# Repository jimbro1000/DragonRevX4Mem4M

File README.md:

# Dragon 256 rev X4 Plus Memory Card #

This repository contains the hardware design
for a heavily revised Dragon 32 computer
memory board.

The design is most definitely experimental
and absolutely unproven

## Design ##

The board replaces the onboard memory
configuration used in early rev X4 PCBs

The bus connection supports a hypothetical
16MB but this is not currently practical

Even with 4MB on this card that main board
only contains logic to address 1MB but will
be expanded to control the full 4MB ASAP.

The remaining 12MB is intended for expansion
slots.

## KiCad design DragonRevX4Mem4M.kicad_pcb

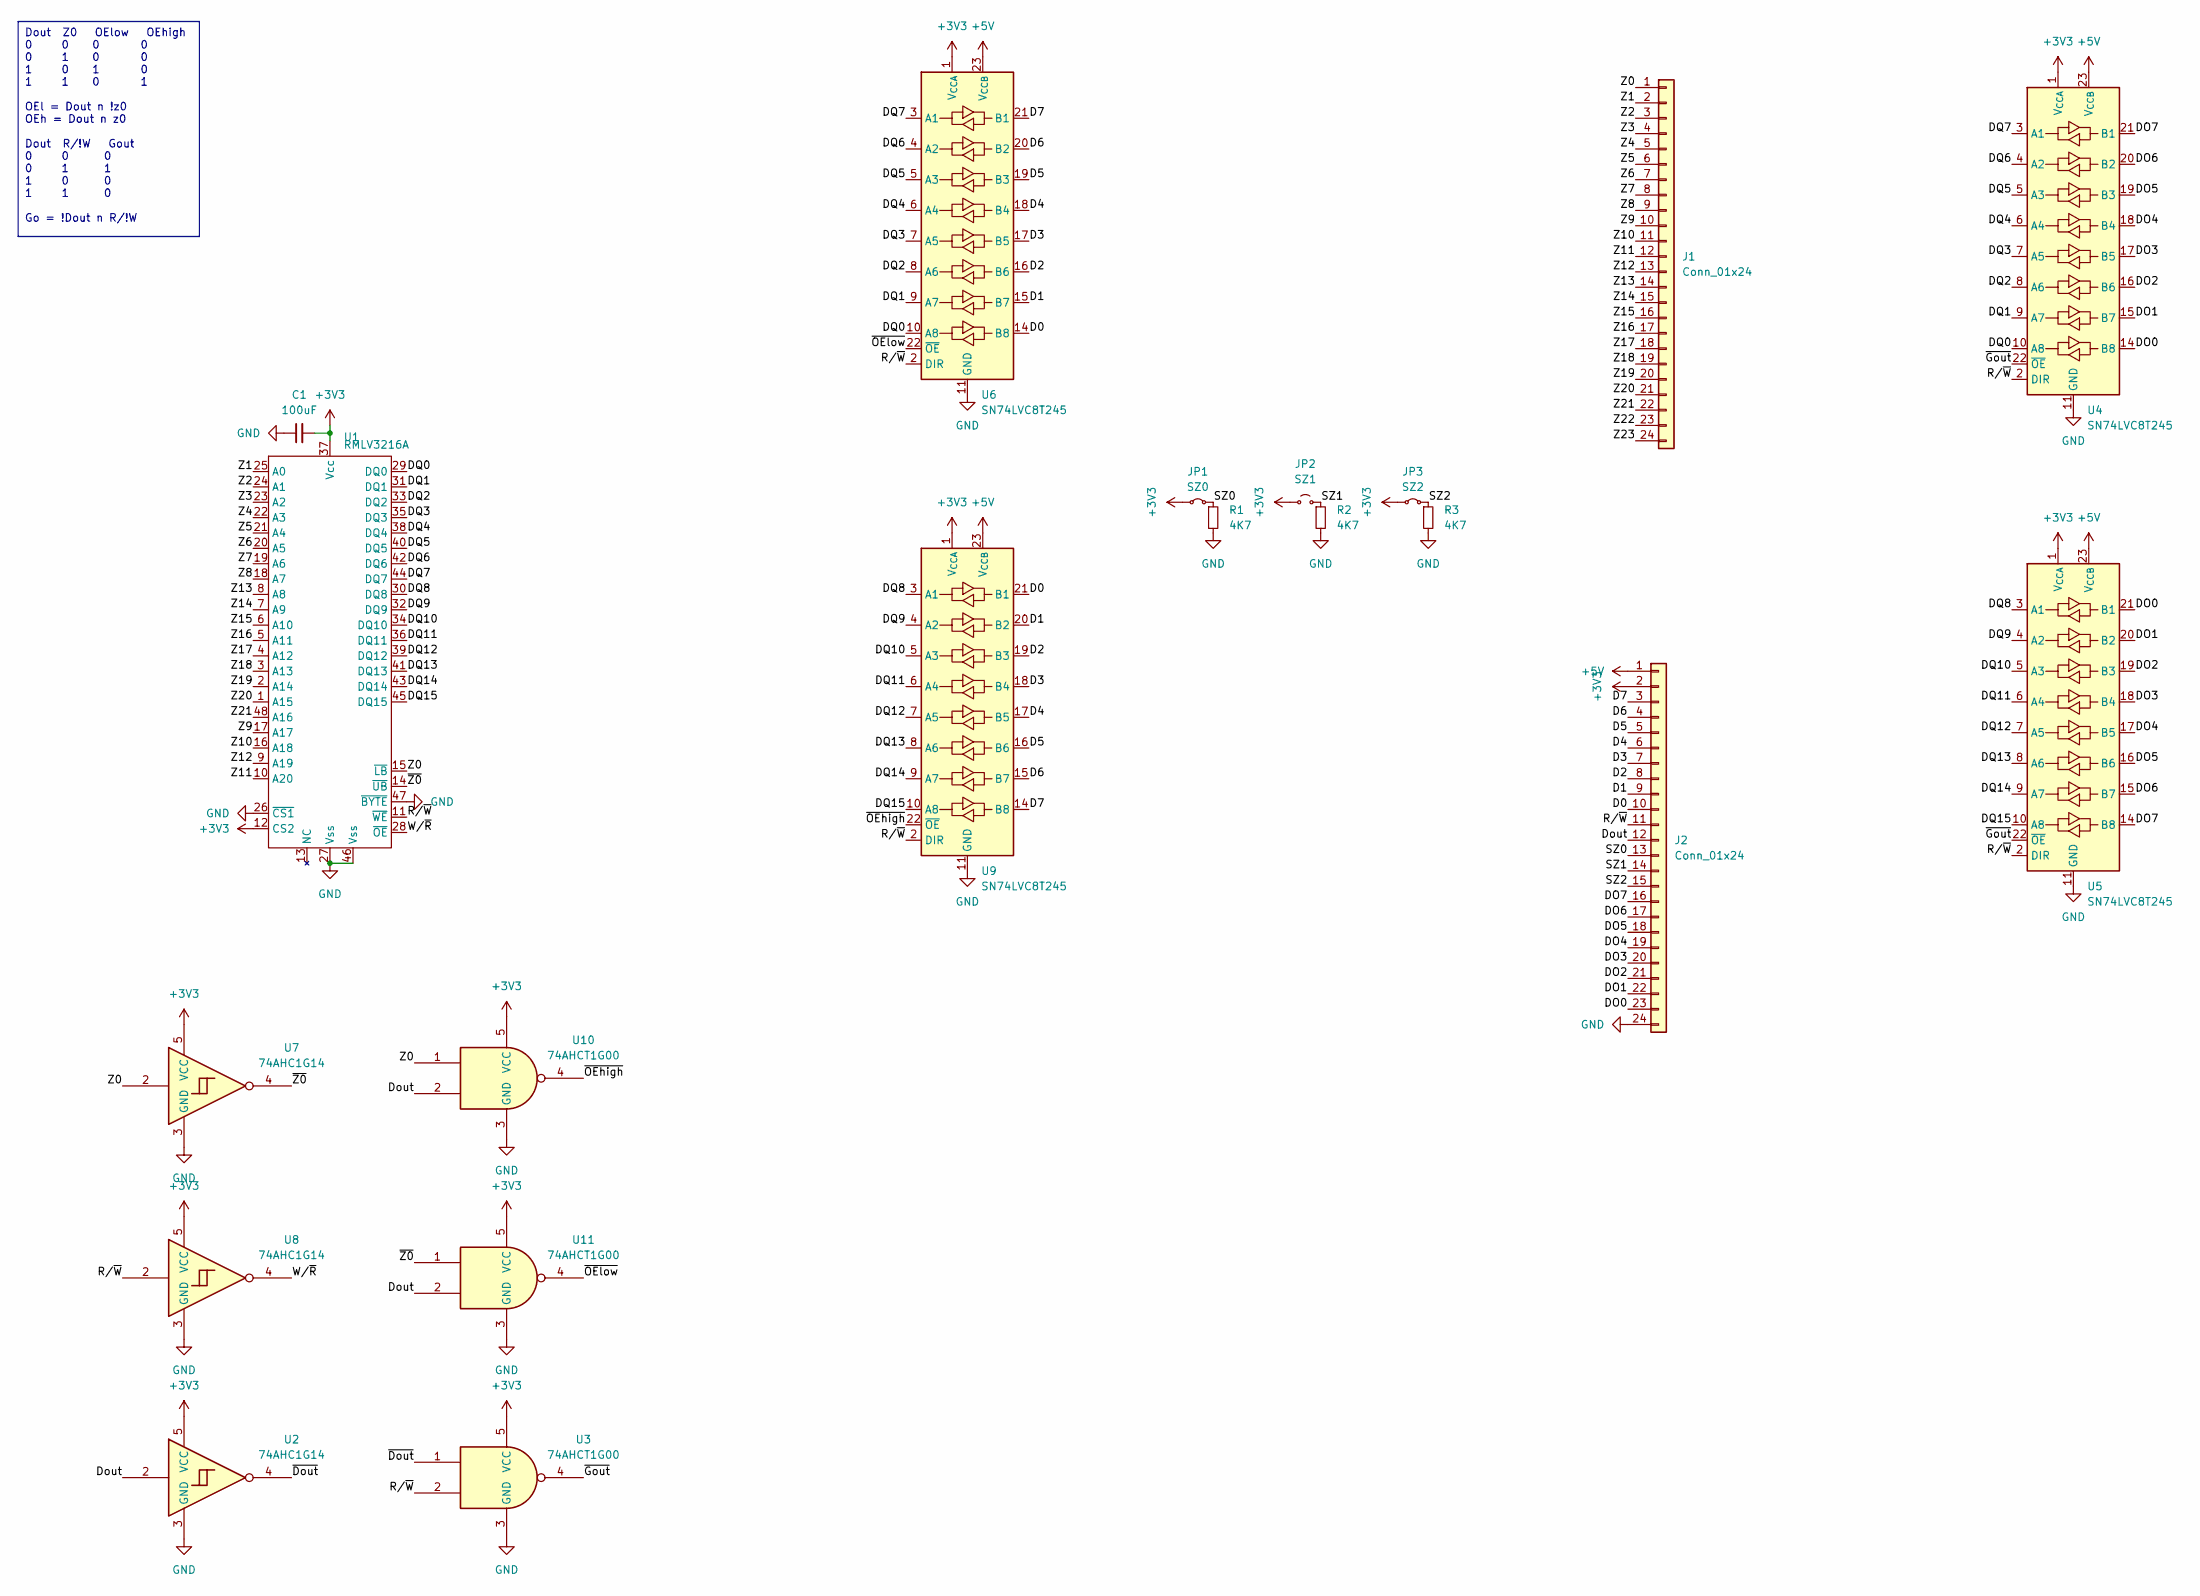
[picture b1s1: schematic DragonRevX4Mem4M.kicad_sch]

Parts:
C1: 100uF; C_0805_2012Metric
J1, J2: Conn_01x24; PinHeader_1x24_P1.27mm_Vertical
JP1: SZ0; SolderJumper-2_P1.3mm_Bridged_Pad1.0x1.5mm
JP2: SZ1; SolderJumper-2_P1.3mm_Open_Pad1.0x1.5mm
JP3: SZ2; SolderJumper-2_P1.3mm_Bridged_Pad1.0x1.5mm
R1, R2, R3: 4K7; C_0603_1608Metric
U1: RMLV3216A; TSOP-I-48_18.4x12mm_P0.5mm; DigiKey RMLV3216AGSA-5S2#AA0-ND
U2, U7, U8: 74AHC1G14; SOT-23-5_HandSoldering; DigiKey 296-1112-1-ND
U3, U10, U11: 74AHCT1G00; SOT-23-5_HandSoldering; DigiKey 296-1111-1-ND
U4, U5, U6, U9: SN74LVC8T245; TSSOP-24_4.4x5mm_P0.4mm; DigiKey 1727-4417-1-ND

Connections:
+3V3: C1.2, J2.2, JP1.1 (A), JP2.1 (A), JP3.1 (A), U1.12 (CS2), U1.37 (Vcc), U2.5 (VCC), U3.5 (VCC), U4.1 (V_{CCA}), U5.1 (V_{CCA}), U6.1 (V_{CCA}), U7.5 (VCC), U8.5 (VCC), U9.1 (V_{CCA}), U10.5 (VCC), U11.5 (VCC)
+5V: J2.1, U4.23 (V_{CCB}), U4.24 (V_{CCB}), U5.23 (V_{CCB}), U5.24 (V_{CCB}), U6.23 (V_{CCB}), U6.24 (V_{CCB}), U9.23 (V_{CCB}), U9.24 (V_{CCB})
/D0: J2.10, U6.14 (B8), U9.21 (B1)
/D1: J2.9, U6.15 (B7), U9.20 (B2)
/D2: J2.8, U6.16 (B6), U9.19 (B3)
/D3: J2.7, U6.17 (B5), U9.18 (B4)
/D4: J2.6, U6.18 (B4), U9.17 (B5)
/D5: J2.5, U6.19 (B3), U9.16 (B6)
/D6: J2.4, U6.20 (B2), U9.15 (B7)
/D7: J2.3, U6.21 (B1), U9.14 (B8)
/DO0: J2.23, U4.14 (B8), U5.21 (B1)
/DO1: J2.22, U4.15 (B7), U5.20 (B2)
/DO2: J2.21, U4.16 (B6), U5.19 (B3)
/DO3: J2.20, U4.17 (B5), U5.18 (B4)
/DO4: J2.19, U4.18 (B4), U5.17 (B5)
/DO5: J2.18, U4.19 (B3), U5.16 (B6)
/DO6: J2.17, U4.20 (B2), U5.15 (B7)
/DO7: J2.16, U4.21 (B1), U5.14 (B8)
/DQ0: U1.29 (DQ0), U4.10 (A8), U6.10 (A8)
/DQ1: U1.31 (DQ1), U4.9 (A7), U6.9 (A7)
/DQ2: U1.33 (DQ2), U4.8 (A6), U6.8 (A6)
/DQ3: U1.35 (DQ3), U4.7 (A5), U6.7 (A5)
/DQ4: U1.38 (DQ4), U4.6 (A4), U6.6 (A4)
/DQ5: U1.40 (DQ5), U4.5 (A3), U6.5 (A3)
/DQ6: U1.42 (DQ6), U4.4 (A2), U6.4 (A2)
/DQ7: U1.44 (DQ7), U4.3 (A1), U6.3 (A1)
/DQ8: U1.30 (DQ8), U5.3 (A1), U9.3 (A1)
/DQ9: U1.32 (DQ9), U5.4 (A2), U9.4 (A2)
/DQ10: U1.34 (DQ10), U5.5 (A3), U9.5 (A3)
/DQ11: U1.36 (DQ11), U5.6 (A4), U9.6 (A4)
/DQ12: U1.39 (DQ12), U5.7 (A5), U9.7 (A5)
/DQ13: U1.41 (DQ13), U5.8 (A6), U9.8 (A6)
/DQ14: U1.43 (DQ14), U5.9 (A7), U9.9 (A7)
/DQ15: U1.45 (DQ15), U5.10 (A8), U9.10 (A8)
/Dout: J2.12, U2.2, U10.2, U11.2
/R/~W: J2.11, U1.11 (~WE), U3.2, U4.2 (DIR), U5.2 (DIR), U6.2 (DIR), U8.2, U9.2 (DIR)
/SZ0: J2.13, JP1.2 (B), R1.1
/SZ1: J2.14, JP2.2 (B), R2.1
/SZ2: J2.15, JP3.2 (B), R3.1
/W/~R: U1.28 (~OE), U8.4
/Z0: J1.1, U1.15 (~LB), U7.2, U10.1
/Z1: J1.2, U1.25 (A0)
/Z2: J1.3, U1.24 (A1)
/Z3: J1.4, U1.23 (A2)
/Z4: J1.5, U1.22 (A3)
/Z5: J1.6, U1.21 (A4)
/Z6: J1.7, U1.20 (A5)
/Z7: J1.8, U1.19 (A6)
/Z8: J1.9, U1.18 (A7)
/Z9: J1.10, U1.17 (A17)
/Z10: J1.11, U1.16 (A18)
/Z11: J1.12, U1.10 (A20)
/Z12: J1.13, U1.9 (A19)
/Z13: J1.14, U1.8 (A8)
/Z14: J1.15, U1.7 (A9)
/Z15: J1.16, U1.6 (A10)
/Z16: J1.17, U1.5 (A11)
/Z17: J1.18, U1.4 (A12)
/Z18: J1.19, U1.3 (A13)
/Z19: J1.20, U1.2 (A14)
/Z20: J1.21, U1.1 (A15)
/Z21: J1.22, U1.48 (A16)
/Z22: J1.23
/Z23: J1.24
/~Dout: U2.4, U3.1
/~Gout: U3.4, U4.22 (~OE), U5.22 (~OE)
/~OEhigh: U9.22 (~OE), U10.4
/~OElow: U6.22 (~OE), U11.4
/~Z0: U1.14 (~UB), U7.4, U11.1
GND: C1.1, J2.24, R1.2, R2.2, R3.2, U1.26 (~CS1), U1.27 (Vss), U1.46 (Vss), U1.47 (~BYTE), U2.3 (GND), U3.3 (GND), U4.11 (GND), U4.12 (GND), U4.13 (GND), U5.11 (GND), U5.12 (GND), U5.13 (GND), U6.11 (GND), U6.12 (GND), U6.13 (GND), U7.3 (GND), U8.3 (GND), U9.11 (GND), U9.12 (GND), U9.13 (GND), U10.3 (GND), U11.3 (GND)

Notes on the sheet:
Dout Z0 OElow OEhigh 0 0 0 0 0 1 0 0 1 0 1 0 1 1 0 1 OEl = Dout n !z0 OEh = Dout n z0 Dout R/!W Gout 0 0 0 0 1 1 1 0 0 1 1 0 Go = !Dout n R/!W

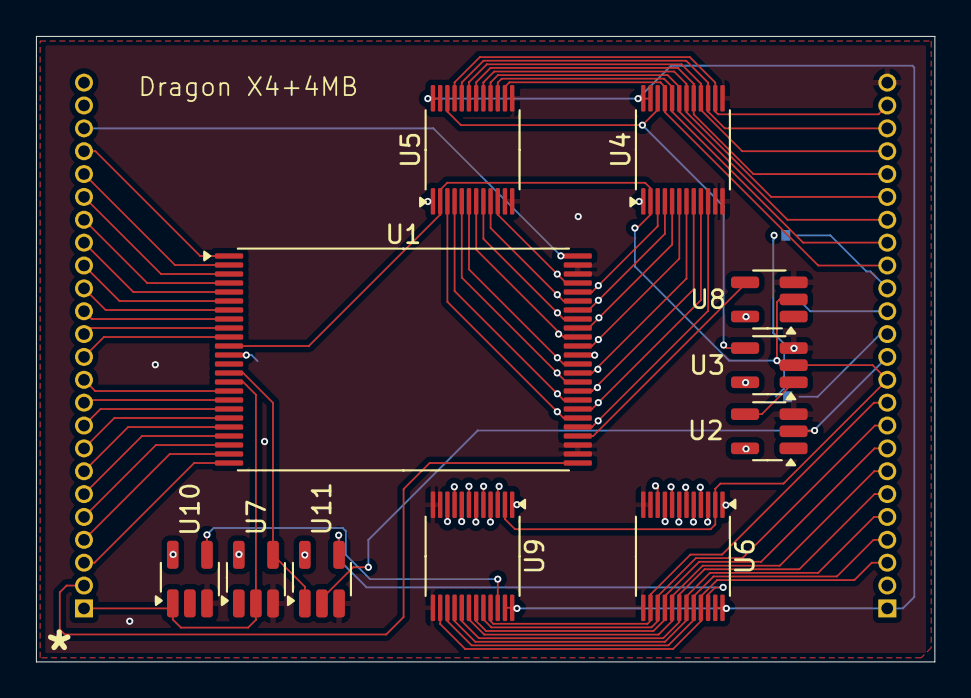
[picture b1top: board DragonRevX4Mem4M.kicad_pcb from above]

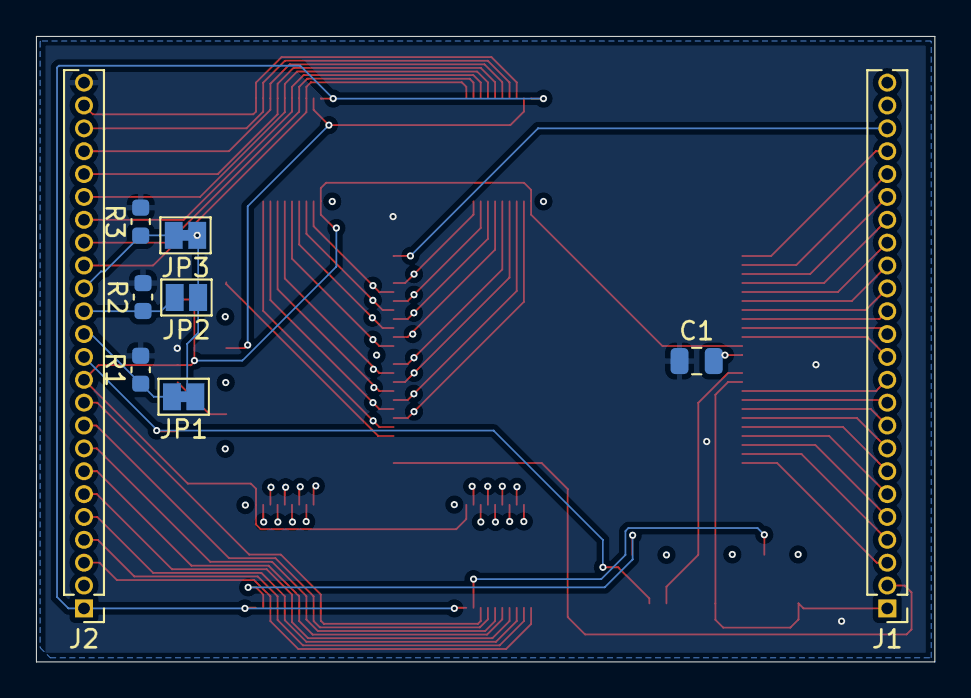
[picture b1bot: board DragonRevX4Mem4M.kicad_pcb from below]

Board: 4 copper layers, 49.9 x 34.7 mm, 20 parts (9 on the bottom side), 68 nets.
